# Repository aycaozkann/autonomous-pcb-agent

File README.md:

# pcb-agent — kart vitrini

**KiCad üzerinde çalışan, yapay zeka destekli PCB tasarım ajanı. Her adımı ölçer, eksiğini raporlar.**

Bu depo ajanın ürettiği **kartları ve sonuçlarını** gösterir. Ajanın kendisi (araç seti) burada yok.

> **Neden private:** Araç seti, üçüncü taraf üretici belgeleri ve ekip çalışmasından gelen geçmiş içerdiği için şimdilik private; kartlar ve sonuçları açık.

## Kartlar

| Kart | Tür | DRC / ERC (2026-10-15, kicad-cli 10.0.4) |
|---|---|---|
| [`kartlar/sht35-breakout`](kartlar/sht35-breakout) | 2 katmanlı SMD breakout, Sensirion SHT35 | 0 ihlal, 0 bağlantısız / 0 ihlal |
| [`kartlar/akilli-enerji-karbon-takip`](kartlar/akilli-enerji-karbon-takip) | Elle lehimlenen THT prototip, ESP32 + AC ölçüm | 0 ihlal, 0 bağlantısız / 0 ihlal |

Her kart klasöründe KiCad kaynakları, Gerber/delik, BOM, CPL, DRC/ERC raporları ve (varsa) şematik/blok
diyagram/hesap belgeleri bulunur. Rapor dosyaları klasörlerin `reports/` altındadır; kendiniz de
`kicad-cli pcb drc` / `kicad-cli sch erc` ile yeniden üretebilirsiniz.

## Araç seti ne yapar (kısaca)

- Şematik ve PCB üzerinde ERC/DRC (`kicad-cli` sarmalayıcısı) ile ek geometri, DFM ve IPC kontrollerini kapı olarak koşar.
- Çalışmayan veya kapsam dışı kalan bir kontrolü "geçti" saymaz; `NO_COVERAGE` olarak raporlar.
- Elle lehimlenecek şematiklerde, bağlantının etiketle değil gerçek telle çizilmesini zorlar.
- Gerber, BOM, CPL ve STEP çıktıları üretir.
- Test paketi: 2026-10-15 tam koşumunda 4022 test: 3930 geçti, 0 başarısız, 0 hata, 92 atlandı (atlananlar ortam bağımlı: canlı KiCad IPC, `pcbnew`, symlink izni vb. — nedenleri tek tek kaydedilmedi). Windows 10, Python 3.14, KiCad 10.0.4.

Ajan bir LLM oturumu (Claude Code) tarafından sürülür; araç seti her adımı ölçer. Kararlar ve
fiziksel doğrulama (montaj, bring-up) insana aittir.

## Sınırlamalar

Bilinen sorunlar (düzeltilmedi, olduğu gibi kayıtlı):

1. **`--schematic-parity` boş PASS verebilir.** DRC kapısı geçici klasöre yalnızca `.kicad_pcb`
   (+ `.kicad_pro`) kopyalıyor, `.kicad_sch`'yi kopyalamıyor. Şematik olmadan KiCad parity listesini
   boş döndürüyor; yani "0 parity farkı — PASS" şematik–PCB uyumunun kanıtı **değildir**. Aynı kartta
   `kicad-cli` şematikle 35 uyarı verirken yalnız PCB ile 0 veriyor.
2. **El-lehim tel kapısı alt sayfalardaki etiket bağlantısını görmüyor.** `etiketle-baglama`
   hata fikstürü, kapıya `--force` verilince **GREEN** çıkıyor (tel=0, etiket=0): kapı yalnızca kök
   sayfayı ölçüyor. Bu fikstür beklenen RED'i göstermez.

Diğer sınırlar:

- Araç seti tek başına kart üretmez; kart-özel betikleri bir LLM oturumu yazar. Karmaşık kartlarda
  yönlendirme ihlalsiz kapanmayabilir (döngü bu durumda "insan gerekli" der).
- Empedans/stackup çözücü sign-off değildir.
- JLCPCB'nin online DFM kontrolü otomatik değil, manuel adımdır.
- Yukarıdaki iki kart basittir ve fiziksel olarak üretilip ölçülmüş değildir (bring-up kaydı yok).

## Lisans

Kart tasarımları **CERN-OHL-P-2.0** altındadır (`LICENSE`). KiCad kütüphane notu ve üretici belge
bağlantıları her kartın kendi README'sindedir.

## İletişim

📬 [ozkanayca8@gmail.com](mailto:ozkanayca8@gmail.com) · [LinkedIn](https://www.linkedin.com/in/ay%C3%A7a-%C3%B6zkan-0a2265195)

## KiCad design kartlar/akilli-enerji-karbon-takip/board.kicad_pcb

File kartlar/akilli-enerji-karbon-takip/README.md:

# Akıllı Enerji ve Karbon Takip Sistemi (el-lehim prototipi)

ESP32-WROOM-32E tabanlı, şebeke gerilimli (AC giriş/çıkış) enerji ölçüm prototipi: ACS712 akım
modülü, 5 V röle modülü, HLK-PM01 besleme, sigortalı AC girişi. Delikli (THT) yapıdadır ve
**elle lehimlenmek üzere** tasarlandı: şematikte her bağlantı etiketle değil çizili telle gösterilir.

> **Güvenlik:** Kartta şebeke gerilimi bölgesi vardır. Yalnızca yetkin kişilerce, uygun
> yalıtım ve koruma ile kullanılmalıdır.

## Doğrulama (2026-10-15, kicad-cli 10.0.4)

| Kontrol | Sonuç | Rapor |
|---|---|---|
| DRC | 0 ihlal, 0 bağlantısız | `reports/drc_2026-10-15.json` |
| ERC | 0 ihlal | `reports/erc_2026-10-15.json` |

## İçerik

- `board.kicad_{pro,sch,pcb}`, `block_diagram.kicad_sch` — KiCad 10 kaynakları
- `gerbers/`, `bom/`, `pnp/` — üretim çıktıları (2026-09-28; kart dosyası bundan eskidir, 2026-09-25). Bu kart için yeniden üretilmiş bir set yoktur.
- `docs/` — blok diyagram, veri sayfası ve mühendislik hesapları (xlsx/csv)
- `reports/` — DRC/ERC çıktıları
- `pin_baglanti_tablosu.md`, `PROJE_GEREKSINIMLERI.md` — tasarım notları

## KiCad kütüphane notu

Bu kart KiCad 10 ile çizildi ve **standart KiCad sembol/footprint kütüphanelerini** kullanır
(kartla birlikte dağıtılmaz). Projeyi açarken KiCad'in kendi kütüphanelerinin kurulu olması
gerekir. Kütüphane tabloları (`fp-lib-table`) Windows'taki varsayılan kurulum yolunu
(`C:/Program Files/KiCad/10.0/...`) gösteriyor olabilir; başka bir sistemde
*Tercihler → Footprint Kütüphanelerini Yönet* ile kendi yolunuza çevirin.
KiCad kütüphaneleri kendi lisansları (CC-BY-SA 4.0 + istisna) altındadır; bu deponun
CERN-OHL-P-2.0 lisansı yalnızca kartın kendi tasarım dosyalarını kapsar.

## Datasheet bağlantıları

Üretici belgeleri bu depoya **kopyalanmadı**; güncel sürümler üreticilerin sitelerinde:

- Espressif ESP32-WROOM-32E: <https://www.espressif.com/sites/default/files/documentation/esp32-wroom-32e_esp32-wroom-32ue_datasheet_en.pdf>
- Allegro ACS712: <https://www.allegromicro.com/en/products/sense/current-sensor-ics/zero-to-fifty-amp-integrated-conductor-sensor-ics/acs712>
- Hi-Link HLK-PM01: <https://www.hlktech.net/>
- Songle SRD-05VDC-SL-C: <https://www.songlerelay.com/>
- Bulgin FX0456 sigorta yuvası: <https://www.bulgin.com/>
- TDK (FK26X7R1H105KRE06): <https://www.tdk-electronics.tdk.com/>
- MDD 1N5819: <https://www.mdd.com.tw/>

## Lisans

CERN-OHL-P-2.0 — bkz. kökteki `LICENSE`.

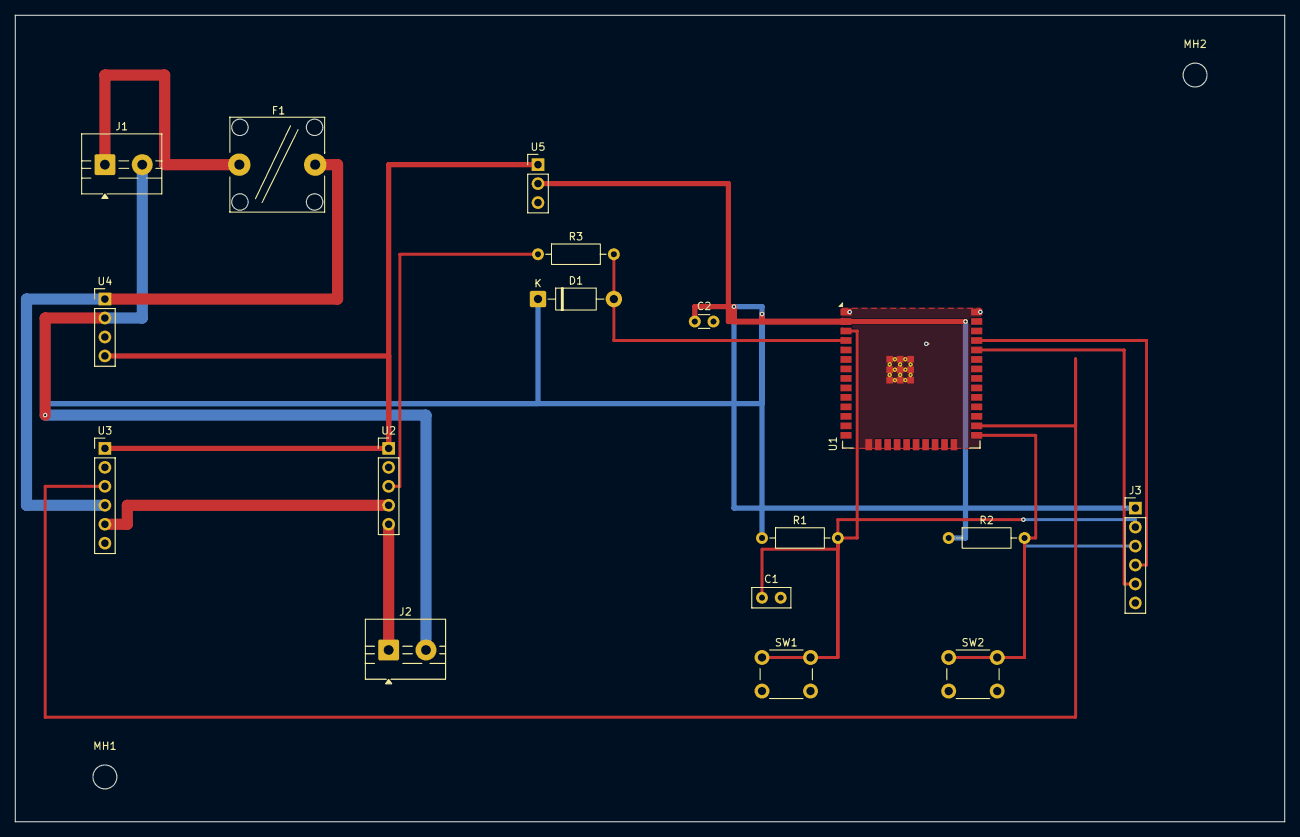
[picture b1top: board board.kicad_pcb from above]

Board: 2 copper layers, 170.0 x 108.0 mm, 19 parts (0 on the bottom side), 15 nets.

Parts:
C1: 1uF; C_Disc_D5.0mm_W2.5mm_P2.50mm
C2: 100nF; C_Disc_D3.0mm_W1.6mm_P2.50mm
D1: 1N5819; D_DO-41_SOD81_P10.16mm_Horizontal
F1: 3.15A 250V hizli atan (5x20mm); Fuseholder_Cylinder-5x20mm_Bulgin_FX0456_Vertical_Closed
J1: AC Giris (L,N); TerminalBlock_MaiXu_MX126-5.0-02P_1x02_P5.00mm
J2: AC Cikis / Yuk (L,N); TerminalBlock_MaiXu_MX126-5.0-02P_1x02_P5.00mm
J3: UART Programlama Header; PinHeader_1x06_P2.54mm_Vertical
MH1, MH2: M3 montaj deligi; MountingHole_3.2mm_M3
R1, R2: 10k; R_Axial_DIN0207_L6.3mm_D2.5mm_P10.16mm_Horizontal
R3: 1k; R_Axial_DIN0207_L6.3mm_D2.5mm_P10.16mm_Horizontal
SW1: EN Reset; SW_PUSH_6mm
SW2: BOOT; SW_PUSH_6mm
U1: ESP32-WROOM-32E
U2: ACS712-05B breakout modul; PinHeader_1x05_P2.54mm_Vertical
U3: 5V role modulu (SRD-05VDC-SL-C tabanli); PinHeader_1x06_P2.54mm_Vertical
U4: HLK-PM01; PinHeader_1x04_P2.54mm_Vertical
U5: AMS1117-3.3 breakout modul; PinHeader_1x03_P2.54mm_Vertical

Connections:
+3V3: C2.1, D1.1, J3.1, R1.1, R2.1, U1.2, U5.2
+5V: U2.1, U3.1, U4.4, U5.1
ACS_OUT: R3.1, U2.3
ACS_OUT_PROT: D1.2, R3.2, U1.4
AC_L_FUSED: F1.2, U3.4, U4.1
AC_L_IN: F1.1, J1.1
AC_L_LOAD: J2.1, U2.5
AC_N: J1.2, J2.2, U4.2
EN: C1.1, J3.2, R1.2, SW1.1, U1.3
GND: C1.2, C2.2, J3.6, SW1.2, SW2.2, U1.1, U1.15, U1.38, U1.39, U2.2, U3.2, U4.3, U5.3
GPIO0: J3.3, R2.2, SW2.1, U1.25
RELAY_CTRL: U1.26, U3.3
RELAY_NO_ACS_IPP: U2.4, U3.5
UART_RX: J3.5, U1.34
UART_TX: J3.4, U1.35

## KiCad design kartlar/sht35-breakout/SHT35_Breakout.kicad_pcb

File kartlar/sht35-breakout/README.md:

# SHT35 Breakout (Rev. 4)

Sensirion SHT35-DIS sıcaklık/nem sensörü için 2 katmanlı, 1×6 header'lı breakout kartı:
+5V besleme (LDO yok), I²C pull-up'ları, ADDR kartta 10 kΩ ile GND'ye sabitli (adres 0x44),
NRESET ve ALERT header'a çıkıyor.

## Doğrulama (2026-10-15, kicad-cli 10.0.4)

| Kontrol | Sonuç | Rapor |
|---|---|---|
| DRC | 0 ihlal, 0 bağlantısız | `reports/drc_2026-10-15.json` |
| ERC | 0 ihlal | `reports/erc_2026-10-15.json` |

## İçerik

- `SHT35_Breakout.kicad_{pro,sch,pcb}` — KiCad 10 kaynakları
- `gerbers/` — Gerber + delik dosyası (`SHT35_Breakout.drl`), bu depodaki kartın güncel hâlinden 2026-10-15'te üretildi
- `bom/`, `pnp/` — BOM ve yerleşim (CPL) dosyaları
- `docs/` — şematik PDF, kart görünümü PDF, STEP modeli
- `pin_baglanti_tablosu.md` — tasarım notları (içindeki `DATASHEETS/…` yolları depoda yoktur, aşağıdaki bağlantılara bakın)

## KiCad kütüphane notu

Bu kart KiCad 10 ile çizildi ve **standart KiCad sembol/footprint kütüphanelerini** kullanır
(kartla birlikte dağıtılmaz). Projeyi açarken KiCad'in kendi kütüphanelerinin kurulu olması
gerekir. Kütüphane tabloları (`fp-lib-table`) Windows'taki varsayılan kurulum yolunu
(`C:/Program Files/KiCad/10.0/...`) gösteriyor olabilir; başka bir sistemde
*Tercihler → Footprint Kütüphanelerini Yönet* ile kendi yolunuza çevirin.
KiCad kütüphaneleri kendi lisansları (CC-BY-SA 4.0 + istisna) altındadır; bu deponun
CERN-OHL-P-2.0 lisansı yalnızca kartın kendi tasarım dosyalarını kapsar.

## Datasheet bağlantıları

Üretici belgeleri bu depoya **kopyalanmadı**; güncel sürümler üreticilerin sitelerinde:

- Sensirion SHT35-DIS-B: <https://sensirion.com/products/catalog/SHT35-DIS-B>
- Yageo (CC0603KRX7R9BB104, RC0603FR-074K7L, RC0603FR-0710KL): <https://www.yageo.com/>

## Lisans

CERN-OHL-P-2.0 — bkz. kökteki `LICENSE`.

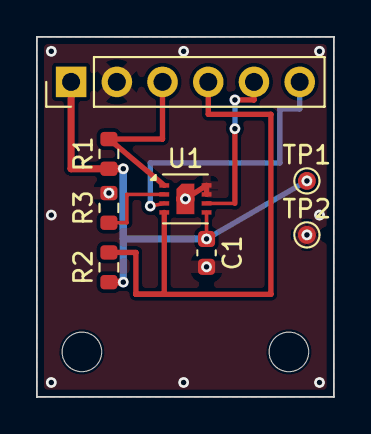
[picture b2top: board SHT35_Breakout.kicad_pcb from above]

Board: 2 copper layers, 16.5 x 20.0 mm, 10 parts (0 on the bottom side), 7 nets.

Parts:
C1: 100nF; C_0603_1608Metric
J1: Conn_01x06; PinHeader_1x06_P2.54mm_Vertical
MH1, MH2: MountingHole_2.2mm_M2
R1, R2: 4.7k; R_0603_1608Metric
R3: 10k; R_0603_1608Metric
TP1: +5V; TestPoint_Pad_D1.0mm
TP2: GND; TestPoint_Pad_D1.0mm
U1: SHT35-DIS; Sensirion_DFN-8-1EP_2.5x2.5mm_P0.5mm_EP1.1x1.7mm

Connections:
+5V: C1.1, J1.1, R1.1, R2.1, TP1.1, U1.5
GND: C1.2, J1.2, R3.2, TP2.1, U1.7, U1.8, U1.9
I2C_ADDR: R3.1, U1.2
I2C_SCL: J1.4, R2.2, U1.4
I2C_SDA: J1.3, R1.2, U1.1
SHT_ALERT: J1.6, U1.3
SHT_NRESET: J1.5, U1.6

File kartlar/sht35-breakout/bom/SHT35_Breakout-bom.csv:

"Reference","Value","Footprint","Qty","MPN","Manufacturer","LCSC"
"C1","100nF","Capacitor_SMD:C_0603_1608Metric","1","CC0603KRX7R9BB104","Yageo","C14663"
"J1","Conn_01x06","Connector_PinHeader_2.54mm:PinHeader_1x06_P2.54mm_Vertical","1","2.54-1x6P (generic)","Generic/Various (jenerik, birbirinin yerine kullanılabilir)","C37208"
"R1,R2","4.7k","Resistor_SMD:R_0603_1608Metric","2","RC0603FR-074K7L","Yageo","C99782"
"R3","10k","Resistor_SMD:R_0603_1608Metric","1","RC0603FR-0710KL","Yageo","C98220"
"U1","SHT35-DIS","Sensor_Humidity:Sensirion_DFN-8-1EP_2.5x2.5mm_P0.5mm_EP1.1x1.7mm","1","SHT35-DIS-B2.5KS","Sensirion","C90161"
